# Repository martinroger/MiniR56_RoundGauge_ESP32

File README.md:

An ESP32-based OBD Gauge for the R56 Mini Cooper

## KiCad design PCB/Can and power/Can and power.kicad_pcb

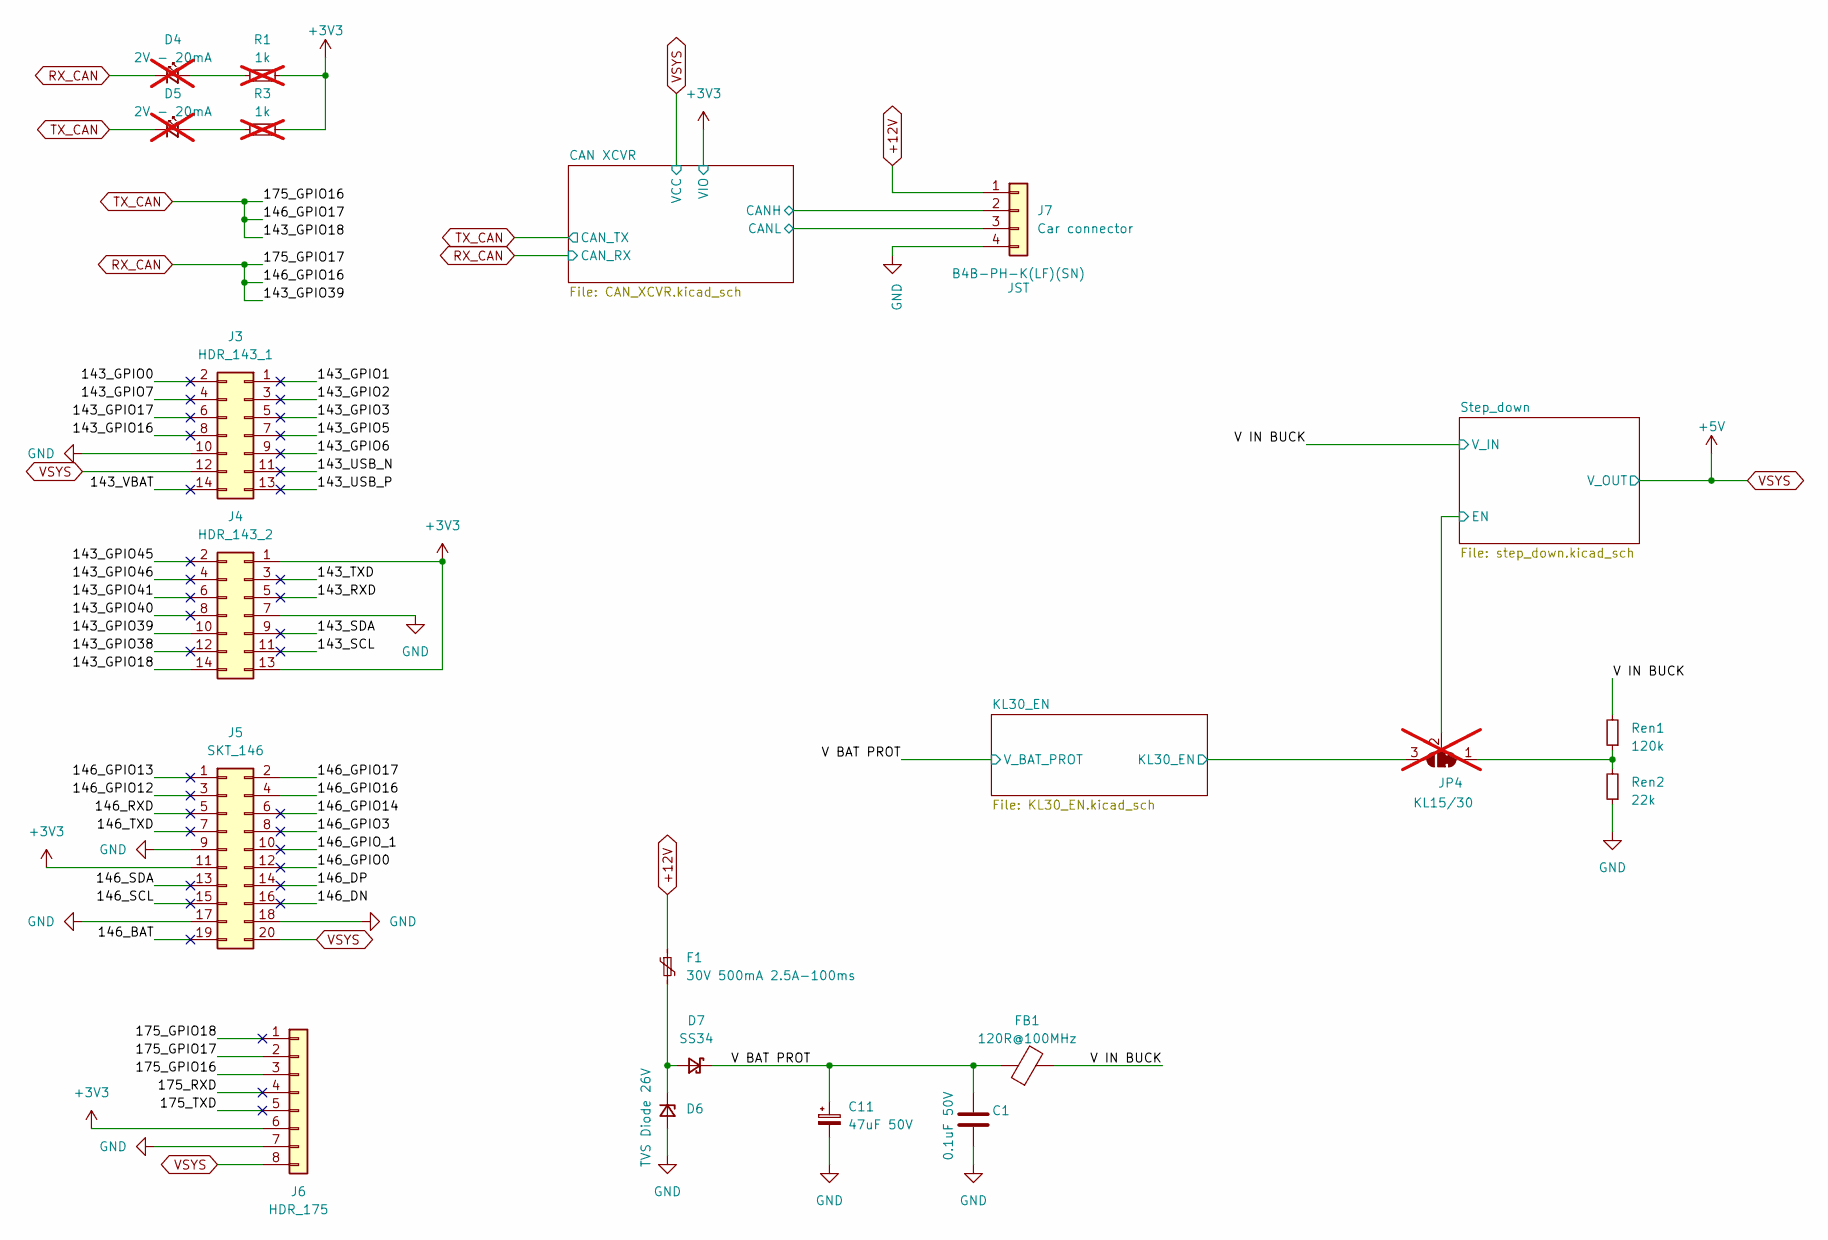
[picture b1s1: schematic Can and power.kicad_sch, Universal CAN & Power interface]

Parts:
C1: 0.1uF 50V; C_0603_1608Metric; Manufacturer_Part_Number CC0603KRX7R9BB104; LCSC alt. C16194176
C11: 47uF 50V; CP_Elec_6.3x7.7; Manufacturer_Part_Number RVT1H470M0607; LCSC C72523
D4, D5: 2V - 20mA; LED_0603_1608Metric; Manufacturer_Part_Number LTST-C190KFKT; LCSC alt. C157740; not fitted
D6: TVS Diode 26V; D_SMB; Manufacturer_Part_Number SMBJ26A; LCSC C19077580
D7: SS34; D_SMA; Manufacturer_Part_Number SS34; LCSC C8678
F1: 30V 500mA 2.5A-100ms; Fuse_1210_3225Metric; Manufacturer_Part_Number MF-USHT050KX; LCSC alt. C720079
FB1: 120R@100MHz; L_0805_2012Metric; Manufacturer_Part_Number BLM21PG121SN1D; LCSC C79382
J3: HDR_143_1; PinHeader_2x07_P1.27mm_Vertical; Manufacturer_Part_Number 20021111-00014T4LF; LCSC alt. C2935955
J4: HDR_143_2; PinHeader_2x07_P1.27mm_Vertical; Manufacturer_Part_Number 20021111-00014T4LF; LCSC alt. C2935955
J5: SKT_146; PinSocket_2x10_P1.27mm_Vertical; Manufacturer_Part_Number LPPB102CFFN-RC; LCSC alt. C22438134
J6: HDR_175; PinHeader_1x08_P2.54mm_Vertical; Manufacturer_Part_Number 61300811121; LCSC alt. C492407
J7: Car connector; JST_PH_B4B-PH-K_1x04_P2.00mm_Vertical; Manufacturer_Part_Number B4B-PH-K(LF)(SN); LCSC alt. C265289
JP4: KL15/30; SolderJumper-3_P1.3mm_Bridged12_RoundedPad1.0x1.5mm; not fitted
R1, R3: 1k; R_0603_1608Metric; Manufacturer_Part_Number 0603WAF1001T5E; LCSC alt. C22548; not fitted
Ren1: 120k; R_0603_1608Metric; Manufacturer_Part_Number 0603WAF1203T5E; LCSC C25808
Ren2: 22k; R_0603_1608Metric; Manufacturer_Part_Number 0603WAF2202T5E; LCSC C31850

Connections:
+3V3: J4.1, J4.13, J5.11, J6.6, R1.2, R3.1; also elsewhere on the board
+12V: F1.1, J7.1
/143_GPIO0: J3.2
/143_GPIO1: J3.1
/143_GPIO2: J3.3
/143_GPIO3: J3.5
/143_GPIO5: J3.7
/143_GPIO6: J3.9
/143_GPIO7: J3.4
/143_GPIO16: J3.8
/143_GPIO17: J3.6
/143_GPIO38: J4.12
/143_GPIO40: J4.8
/143_GPIO41: J4.6
/143_GPIO45: J4.2
/143_GPIO46: J4.4
/143_RXD: J4.5
/143_SCL: J4.11
/143_SDA: J4.9
/143_TXD: J4.3
/143_USB_N: J3.11
/143_USB_P: J3.13
/143_VBAT: J3.14
/146_BAT: J5.19
/146_DN: J5.16
/146_DP: J5.14
/146_GPIO0: J5.12
/146_GPIO3: J5.8
/146_GPIO12: J5.3
/146_GPIO13: J5.1
/146_GPIO14: J5.6
/146_GPIO_1: J5.10
/146_RXD: J5.5
/146_SCL: J5.15
/146_SDA: J5.13
/146_TXD: J5.7
/175_GPIO18: J6.1
/175_RXD: J6.4
/175_TXD: J6.5
/CAN XCVR/CANH: J7.2; also elsewhere on the board
/CAN XCVR/CANL: J7.3; also elsewhere on the board
/KL30_EN/KL30_EN: JP4.3 (B); also elsewhere on the board
/Step_down/EN: JP4.2 (C); also elsewhere on the board
/V BAT PROT: C1.2, C11.1, D7.1 (K), FB1.1; also elsewhere on the board
/V IN BUCK: FB1.2, Ren1.2; also elsewhere on the board
GND: C1.1, C11.2, D6.2 (A), J3.10, J4.7, J5.9, J5.17, J5.18, J6.7, J7.4, Ren2.1; also elsewhere on the board
unnamed: D4.2 (A), R1.1
unnamed: D5.2 (A), R3.2
unnamed: D6.1 (K), D7.2 (A), F1.2
unnamed: JP4.1 (A), Ren1.1, Ren2.2
RX_CAN: D4.1 (K), J4.10, J5.4, J6.2; also elsewhere on the board
TX_CAN: D5.1 (K), J4.14, J5.2, J6.3; also elsewhere on the board
VSYS: J3.12, J5.20, J6.8; also elsewhere on the board

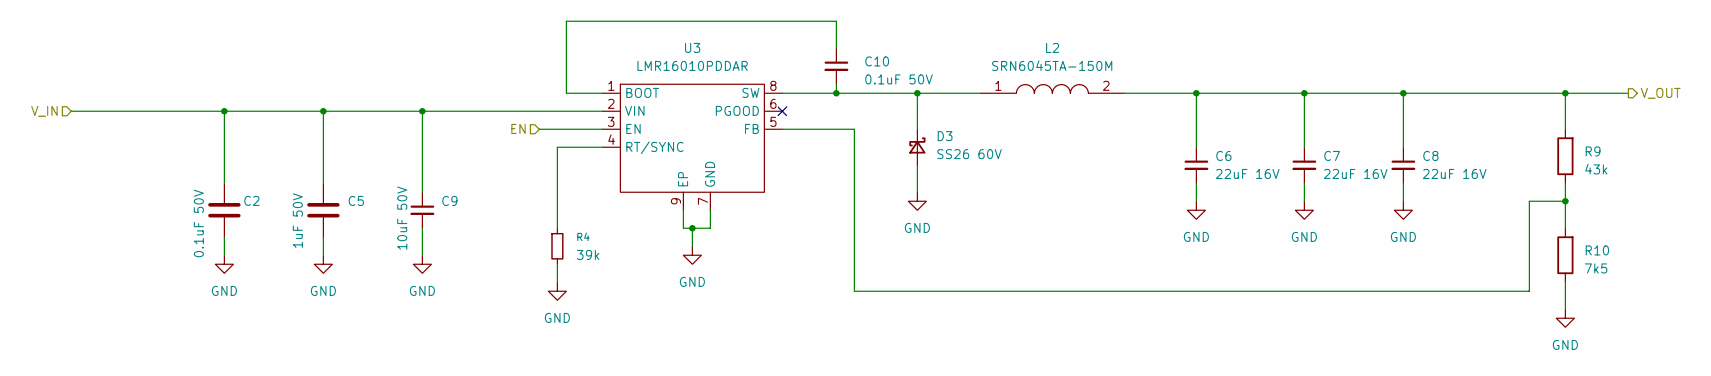
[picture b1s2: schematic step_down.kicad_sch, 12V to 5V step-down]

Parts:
C2: 0.1uF 50V; C_0603_1608Metric; Manufacturer_Part_Number CC0603KRX7R9BB104; LCSC alt. C16194176
C5: 1uF 50V; C_0603_1608Metric; Voltage 25V; Tolerance 10%; Manufacturer_Part_Number CL10A105KB8NNNC; LCSC alt. C15849
C6, C7, C8: 22uF 16V; C_0805_2012Metric; Manufacturer_Part_Number CL21A226MAQNNNE; LCSC C45783
C9: 10uF 50V; C_1206_3216Metric; Manufacturer_Part_Number CL31B106KBHNNNE; LCSC C89632
C10: 0.1uF 50V; C_0603_1608Metric; Manufacturer_Part_Number CC0603KRX7R9BB104; LCSC alt. C108079
D3: SS26 60V; D_SMA; Manufacturer_Part_Number SS26; LCSC C7420363
L2: SRN6045TA-150M; INDC6060X450N; Manufacturer_Part_Number SRN6045TA-150M; Mouser Part Number 652-SRN6045TA-150M
R4: 39k; R_0603_1608Metric; Manufacturer_Part_Number 0603WAF3902T5E; LCSC C23153
R9: 43k; R_0603_1608Metric; Manufacturer_Part_Number 0603WAF4302T5E; LCSC C23172
R10: 7k5; R_0603_1608Metric; Manufacturer_Part_Number 0603WAF7501T5E; LCSC C23234
U3: LMR16010PDDAR; TI_SO-PowerPAD-8_ThermalVias; Manufacturer_Part_Number LMR16010PDDAR; LCSC C183084

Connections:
/Step_down/EN: U3.3 (EN); also elsewhere on the board
/V IN BUCK: C2.2, C5.1, C9.1, U3.2 (VIN); also elsewhere on the board
GND: C2.1, C5.2, C6.2, C7.2, C8.2, C9.2, D3.2 (A), R4.2, R10.1, U3.7 (GND), U3.9 (EP); also elsewhere on the board
unnamed: C10.2, D3.1 (K), L2.1, U3.8 (SW)
unnamed: C10.1, U3.1 (BOOT)
unnamed: R9.1, R10.2, U3.5 (FB)
unnamed: R4.1, U3.4 (RT/SYNC)
VSYS: C6.1, C7.1, C8.1, L2.2, R9.2; also elsewhere on the board

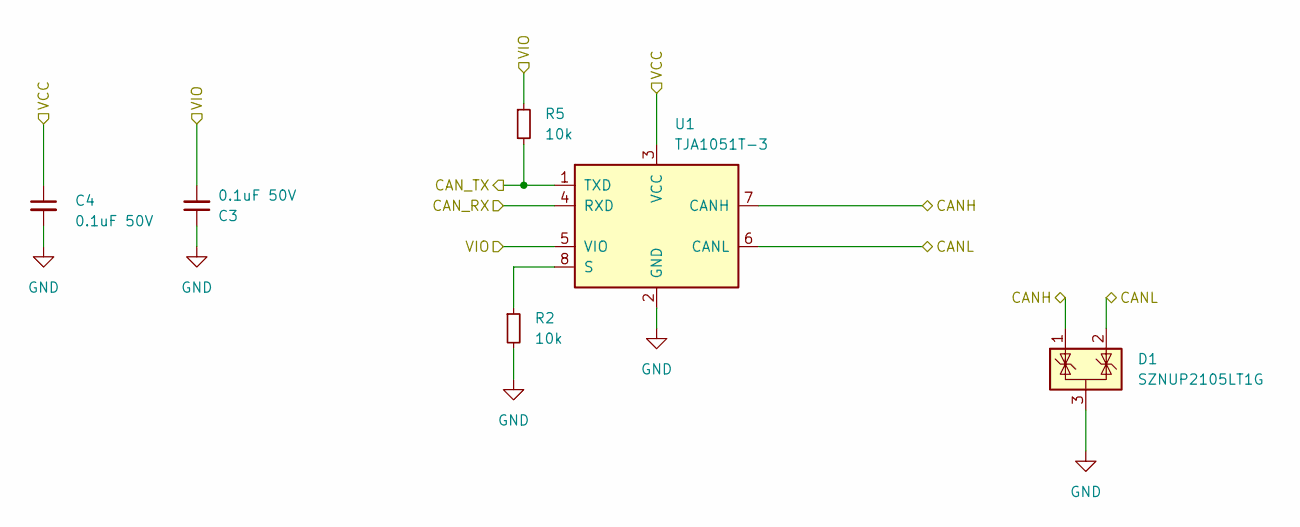
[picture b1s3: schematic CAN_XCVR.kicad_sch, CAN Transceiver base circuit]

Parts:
C3, C4: 0.1uF 50V; C_0603_1608Metric; Manufacturer_Part_Number CC0603KRX7R9BB104; LCSC alt. C108079
D1: SZNUP2105LT1G; SOT-23; Manufacturer_Part_Number SZNUP2105LT1G; LCSC C233494
R2, R5: 10k; R_0603_1608Metric; Manufacturer_Part_Number 0603WAF1002T5E; LCSC C25804
U1: TJA1051T-3; SOIC-8_3.9x4.9mm_P1.27mm; Manufacturer_Part_Number TJA1051T/3/1J; LCSC C38695

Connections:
+3V3: C3.2, R5.1, U1.5 (VIO); also elsewhere on the board
/CAN XCVR/CANH: D1.1 (K), U1.7 (CANH); also elsewhere on the board
/CAN XCVR/CANL: D1.2 (K), U1.6 (CANL); also elsewhere on the board
GND: C3.1, C4.2, D1.3 (A), R2.2, U1.2 (GND); also elsewhere on the board
unnamed: R2.1, U1.8 (S)
RX_CAN: U1.4 (RXD); also elsewhere on the board
TX_CAN: R5.2, U1.1 (TXD); also elsewhere on the board
VSYS: C4.1, U1.3 (VCC); also elsewhere on the board

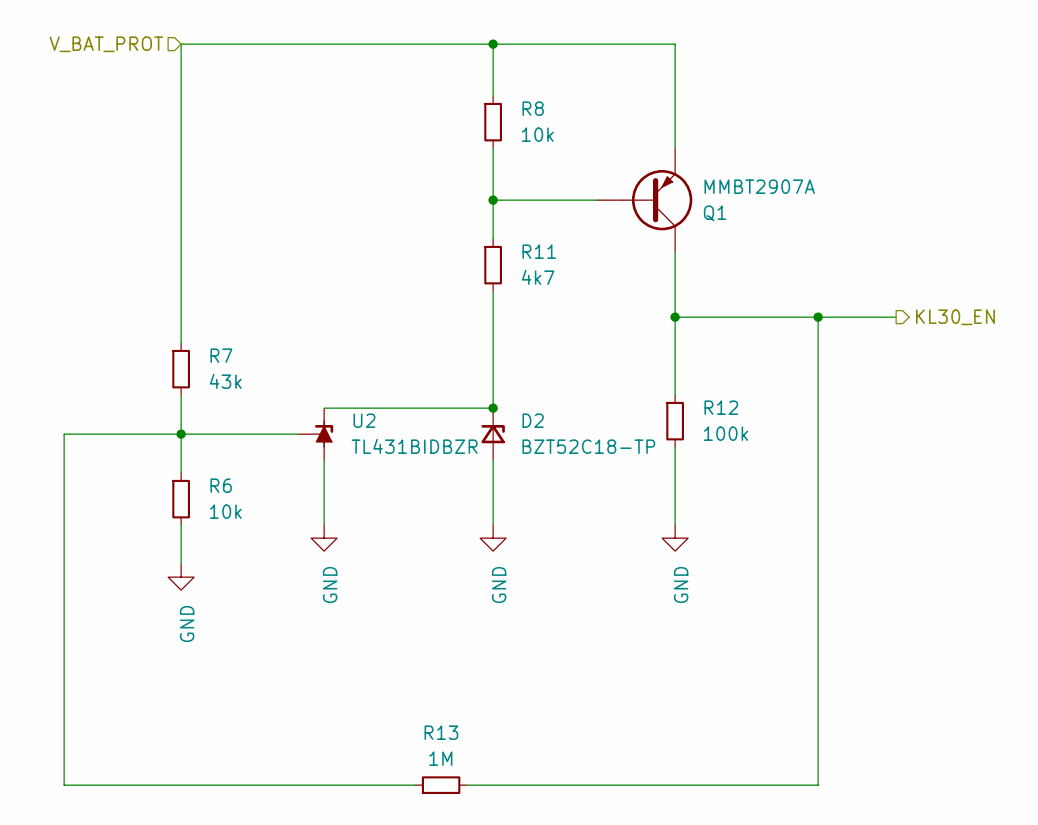
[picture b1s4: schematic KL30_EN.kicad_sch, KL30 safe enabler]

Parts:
D2: BZT52C18-TP; D_SOD-123; Manufacturer_Part_Number BZT52C18; LCSC C19077414
Q1: MMBT2907A; SOT-23; Manufacturer_Part_Number MMBT2907A; LCSC C7420352
R6, R8: 10k; R_0603_1608Metric; Manufacturer_Part_Number 0603WAF1002T5E; LCSC C25804
R7: 43k; R_0603_1608Metric; Manufacturer_Part_Number 0603WAF4302T5E; LCSC C23172
R11: 4k7; R_0603_1608Metric; Manufacturer_Part_Number 0603WAF4701T5E; LCSC C23162
R12: 100k; R_0603_1608Metric; Manufacturer_Part_Number 0603WAF1003T5E; LCSC C25803
R13: 1M; R_0603_1608Metric; Manufacturer_Part_Number 0603WAF1004T5E; LCSC C22935
U2: TL431BIDBZR; SOT-23-3; Manufacturer_Part_Number TL431BIDBZR; LCSC C41283

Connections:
/KL30_EN/KL30_EN: Q1.3 (C), R12.1, R13.2; also elsewhere on the board
/V BAT PROT: Q1.2 (E), R7.1, R8.1; also elsewhere on the board
GND: D2.2 (A), R6.2, R12.2, U2.3 (A); also elsewhere on the board
unnamed: D2.1 (K), R11.2, U2.1 (K)
unnamed: Q1.1 (B), R8.2, R11.1
unnamed: R6.1, R7.2, R13.1, U2.2 (REF)

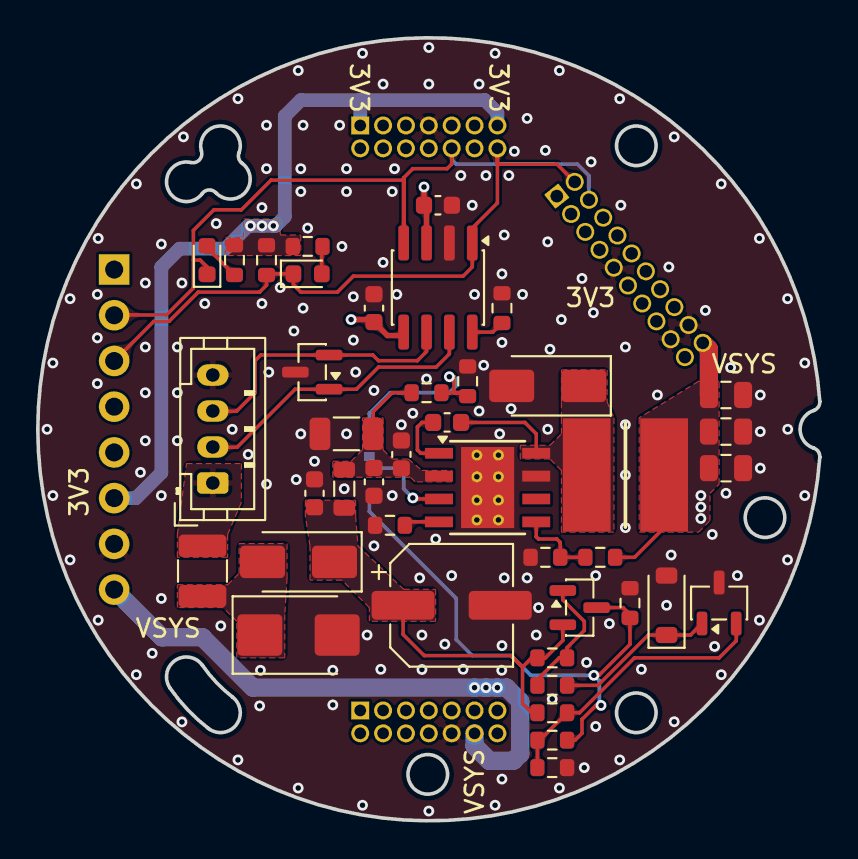
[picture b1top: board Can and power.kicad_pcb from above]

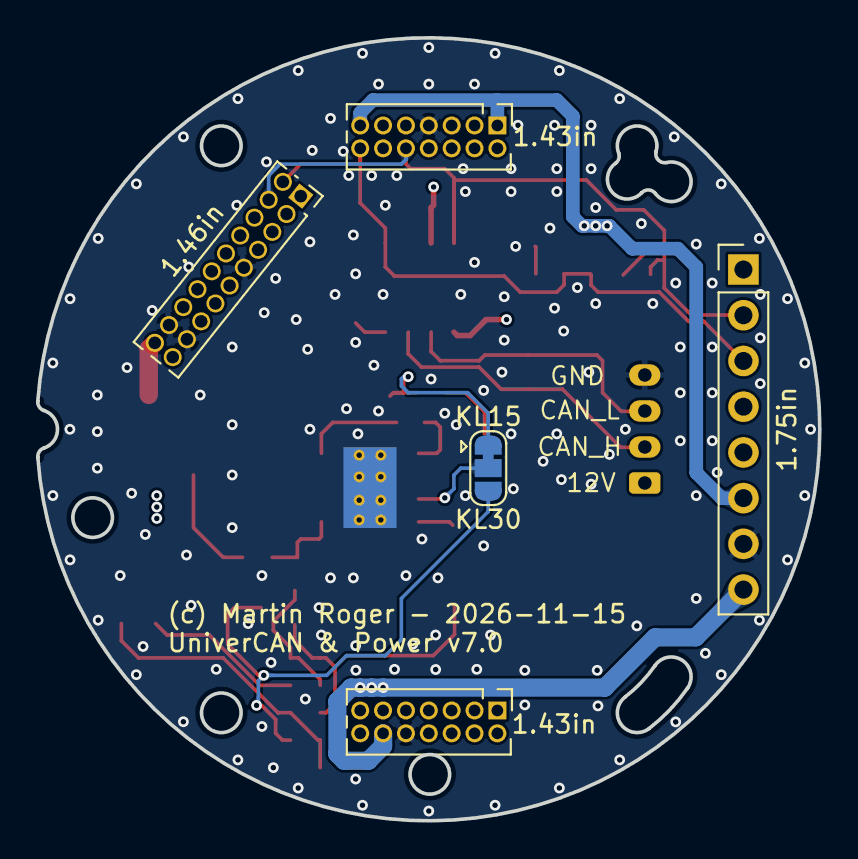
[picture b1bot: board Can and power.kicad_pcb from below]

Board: 4 copper layers, 43.4 x 43.5 mm, 46 parts (5 on the bottom side), 24 nets.

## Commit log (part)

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2024-02-17 Working initial version
2024-02-17 Added more dependencies for accelerometer and touch
2024-02-17 Clean up
2024-02-17 Integrated QMI8658
2024-02-19 Added LVGL 9 binding
2024-02-19 LVGL Working, some buf messages
2024-02-20 Introducing SERIALDEBUG flag
2024-02-20 Displays acceleration
2024-02-20 Moving acceleration dot
2024-02-23 Kinda working version, no refresh
2024-02-23 Am an idiot
2024-03-04 Fonts for reference
2024-03-04 Base version screen
2024-03-04 Small corrections on font and display
2024-03-04 Annotations and start of cleanup
2024-03-04 Added filters Library reference
2024-03-04 Timer implementation
2024-03-04 Updating fake water
2024-03-10 Basic OBD functionality
2024-03-10 Floats are working
2024-03-25 PCB for shield
2024-03-26 Pre-traces
2024-03-27 First PCBWay quotation
2024-03-28 First purchase
2024-04-25 Change of transceiver
    For some reasons the TJA 1044 and 1049 get stuck in Standby mode all the time. Not sure why.
2024-04-25 LED resistor corrections
2024-04-26 Starting work for TWAI support
2024-04-26 Updated with TWAI implementation
2024-04-26 Lazy TWAI implementation
    Implemented TWAI of the ESP32S3 on pins 15 and 16. Still reversible to MCP2515 implementation but eventually that will get squashed out.
2024-04-26 Clean-up code and sch, PCB layout is a WIP
    Code limited to TWAI implementation
    Schematic updated with solder bridges
    PCB layout is a WIP
2024-04-26 Resistor correction
2024-04-27 New shield design
    New shield design. MCP2515 is gone and transceiver has moved to SN65HVD230
    Enable pin on the converter is used to cut off the uC when below 12V. Resistor values may have to change.
    No real protection on start up stage -> might need another layer for that
    Updated INO to reflect the changes in pinout
2024-05-21 Platform 6.7.0 compatibility trial
2024-05-21 Update platformio.ini
    Added release and corrected libraries
2024-05-21 Update main.cpp
    Cut out the CAN bit to focus on LVGL manipulation
2024-05-21 Update main.cpp
    Clock implementation works
    Trying to listen over serial now
2024-05-21 Update main.cpp
    Drawing Arc
    Trying to create an event callback between the text and the arc
2024-05-21 LV Event control of the arc via text value
2024-05-21 EVENT type adjustment
2024-05-21 KNOB adjustment
2024-05-21 Animation works !
2024-05-21 Faffing around with animation parameters
2024-05-22 Transition to EEZ
    Transition to EEZ with new screens. To be noted some aspects of the original build need to be modified a bit to make sure that the whole set of UI files can be generated directly from EEZ.
2024-05-23 Added action_go_to_next_screen to ui.c
2024-05-23 Minor sync
    EVENT_LONG_PRESSED instead of EVENT_PRESSED
2024-05-23 Semi colon correction
2024-05-23 Pre-Styles benchmark
2024-05-23 Styles benchmark
    No impact on RAM
    Minor on Flash (200 bytes)
2024-05-23 Adding arc refresh actions
2024-05-23 Adding functions and animations for arcs
2024-05-23 Value labels can be updated now
2024-05-23 setCanState functionality added
2024-05-23 First OBD test version
2024-06-04 No animate in background, placeholder vals
2024-06-04 Centered text
2024-06-07 Trying to introduce min/max gauges
2024-06-07 CAD reference update
2024-06-07 PoC : Min/Max gauges
2024-06-07 Coolant Scr functions simplification
2024-06-07 Min Maxes for the people !
2024-06-07 No floats, all mins maxs
2024-06-07 10% Animation lag for less frame splitting
2024-06-08 Added protection diode on voltage input
2024-06-08 Create LICENSE
2024-06-08 Added an image
2024-08-07 V4 PCB
    Ren1 and Ren2 values might not be discriminating enough
2024-08-08 Pending corrections on Ren1 and Ren2
    There is a discrepancy in the datasheet and the actual measured voltage hysteresis values. Increasing Ren1 and Ren2 to increase the trigger hysteresis.
2024-08-15 Update platformio.ini
    Locking Release version to latest library versions, aligning debug flag
2024-08-15 Ignition and Key Presence UI assets
    Implementation of booleans and UI labels for absence of Ignition, and absence of key.
2024-08-15 Ignition state and key state handling
    Wordy alerts on screen in case of loss of KL15 or key. No countdown to deep sleep or anything like that yet.
2024-08-15 Commenting
2024-08-15 Update platformio.ini
    Corrections for latest IDF
2024-08-24 Bugfixing
    - Re-export STEP of board with components in 3D
    - Boost gauge limits fixed #4
    - No OBD query if CAN down or key missing #2
    - Wait for successful first read to update screen #5
    - Mishmash delay added (to be removed)
    - Brightness increased to 200 from 128
2024-08-24 Update main.cpp
    - Check startup sequence gibberish shown on screen
2024-08-24 Hiding noise on startup, screen config is isolated
    - #6 is now fixed, solution is to start the screen dark and turn it on later in loop() via normal brightness control
    - Some hint about #7 that it may be a fade-in animation.
    - platformio.ini cleaned up
2024-08-24 Splash screen fixed
    Fixed #7 using differential load animation.
2024-08-24 Fix flickering issue
    Calling AnalogWrite every loop is unreasonable
2024-08-24 Minor cleanup
2024-08-27 Update main.cpp
    Default brightness update
2024-08-31 Prep classes
    KWP class for the main functions
    DID class for the basic DID information container
2024-09-06 Remanning
    Changing approach slightly
2024-09-07 Classes and structs
    - kwpFrame class for basic extended frame
    -kwp class for handling traffic and kwpFrames
    - DID struct to contain the DID definition metrics (could be a class but is a pain in the ass)
2024-09-07 Utils and base DIDs
2024-09-09 Update kwp.h
    Structure work
2024-09-09 Minor changes
    DIDs now store their value.
2024-09-09 KWP fleshing out
    Starting to write methods and sub-logic
2024-09-19 LVGL 9.2 EEz 0.16.1
    Updating to LVGL 9.2.0 and EEZ Studio 0.16.1 plus additional alignments of the ini file
2024-09-19 Update main.cpp
    Starter blending in
2024-10-11 Update platformio.ini
    ArduinoFilters update
2024-10-20 Resolutions
2024-10-20 Not working
2024-10-23 Rectifying board and background panel issues
2024-10-23 Start LVGL 9 port migration
2024-10-23 Continuing port corrections
2024-10-25 Further board and ESP_Panel conf
2024-10-25 Vars definition issue
2024-10-25 Removing vars.h
2024-10-25 Works without mins and maxs
2024-10-25 Touch zones update
2024-10-27 Timers removed
2024-10-27 Introducing vars.c
2024-10-27 MinsMaxs are back in the game
2024-10-27 Animation times and buffer adjustments
2024-10-27 External ANIMATE trigger and lv_timer_handler
2024-10-29 Functional viability
2024-10-29 Direct mode configuration
2024-10-31 Base functionality
2024-11-08 Copying files fro, KWPParser
2024-11-08 Basic KWP pipeline connection
2024-11-08 UI start of rework (non compiled)
2024-11-08 Sub-functions write-up
2024-11-08 Arc functions re-written
2024-11-08 Update screen functions
    Missing still the dataUpdateCB
2024-11-10 DataCB and corrections
2024-11-10 Corrections and base functionality
2024-11-10 Basic corrections, 0x130 basic implementation
2025-01-01 Update platformio.ini
    Moving to pioarduino 51.03.07
2025-03-11 Schematics and PCB update
2025-06-10 Mini VX Dash prototype
2025-06-10 Optimisation
2025-06-10 Buffer size optimisation
2025-06-10 Externalised LV conf
2025-06-10 Frankensteining
2025-06-11 Forgot the second buffer.
2025-06-11 Prep update
2025-06-11 Conversion v8 to v9, step 1
2025-06-11 Compiles, does not work
2025-06-11 Sort of working, TP reset not working, freezing
2025-06-11 Am an idiot
    Maybe mutex must be used all the way/...
2025-06-11 Works, poor performance
2025-06-11 TouchRead issues
2025-06-11 Update lv_conf.h
    Touch works
2025-06-11 Resolved collision between touchRead and mutex
2025-06-11 Pushing performance
2025-06-20 Experimenting with scales
2025-06-29 Works out of the box !
2025-06-29 Speed only
2025-06-29 Expander IO alignments
2025-07-02 Benchmark point vs ESP-IDF
2025-09-01 CanPower v5.1 preparation
2025-09-08 Universal cutout integration
2025-09-08 Partial schematic update
2025-09-08 Pre-PCB layout
2025-09-08 Need ERC corrections
2025-09-08 Projectification, correct footprints
2025-09-08 UniverCan v6.0
2025-09-10 Position refinements
2025-09-10 Cleanup
2025-09-16 Explicit callout to lib version, update to 1.0.4
    Reacting to an issue by @51hhh on the boilerplate repo. Colors are inverted, need to be moved as a PR for correction in the library. (TODO)
2025-09-22 v6.1 placeholder for bulk resistor and capacitor
2025-09-30 Digikey PN
2025-09-30 LCSC BOM finalisation
2025-10-01 Production order v6.1
2025-11-05 First production update
2025-11-30 Support DATA and Savvycan scripts
